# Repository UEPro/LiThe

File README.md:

# LiThe
Lichttheremin / Light-Theremin<br />

This PCB was designed for a Workshop in Germany, thus the documentation is in German. Contact me if you need a translation (Contact info in folder "Documentation", file "Anleitung_LiThe")

<b>AKF-WORKSHOP:</b></n>

Hallo ihr Lieben, ich hoffe ihr hattet alle ein tolles Festival und seid gut Heim gekommen. :)

Vielen Dank, dass ihr beim Workshop mitgemacht habt. Es hat mir riesigen Spaß gemacht, mit euch zu Arbeiten und ich hoffe auch ihr hattet Freude am basteln.

Solltet ihr irgendwelche Fragen oder Probleme haben, schreibt mir einfach über github oder schickt mir eine E-Mail (die Adresse steht in der Anleitung oben im Ordner "Documentation").

Ich werde außerdem eine Facebookseite einrichten, damit ihr mich einfacher kontaktieren könnt. Der Link dazu kommt dann hier her.

Schreibt mir gerne auch für weiteres Feedback und Vorschläge.

Nochmals Danke für die tolle Zeit mit euch und das nette Feedback :) Ich hoffe man sieht sich wieder.

Downloadanleitung:<br />
-Einzelne Datei: Rechtsklick auf die Datei → "Ziel speichern unter" anklicken<br />
-Ganzes Archiv: oben rechts den grünen Knopf "Clone or download" anklicken → "Download as ZIP" anklicken → ZIP Archiv entpacken

<br /><span xmlns:dct="http://purl.org/dc/terms/" property="dct:title">LiThe</span> by <a xmlns:cc="http://creativecommons.org/ns#" href="https://github.com/UEPro/" property="cc:attributionName" rel="cc:attributionURL">Useless Electronics Projects</a> is licensed under a <a rel="license" href="http://creativecommons.org/licenses/by-sa/4.0/">Creative Commons Attribution-ShareAlike 4.0 International License</a>.<br />

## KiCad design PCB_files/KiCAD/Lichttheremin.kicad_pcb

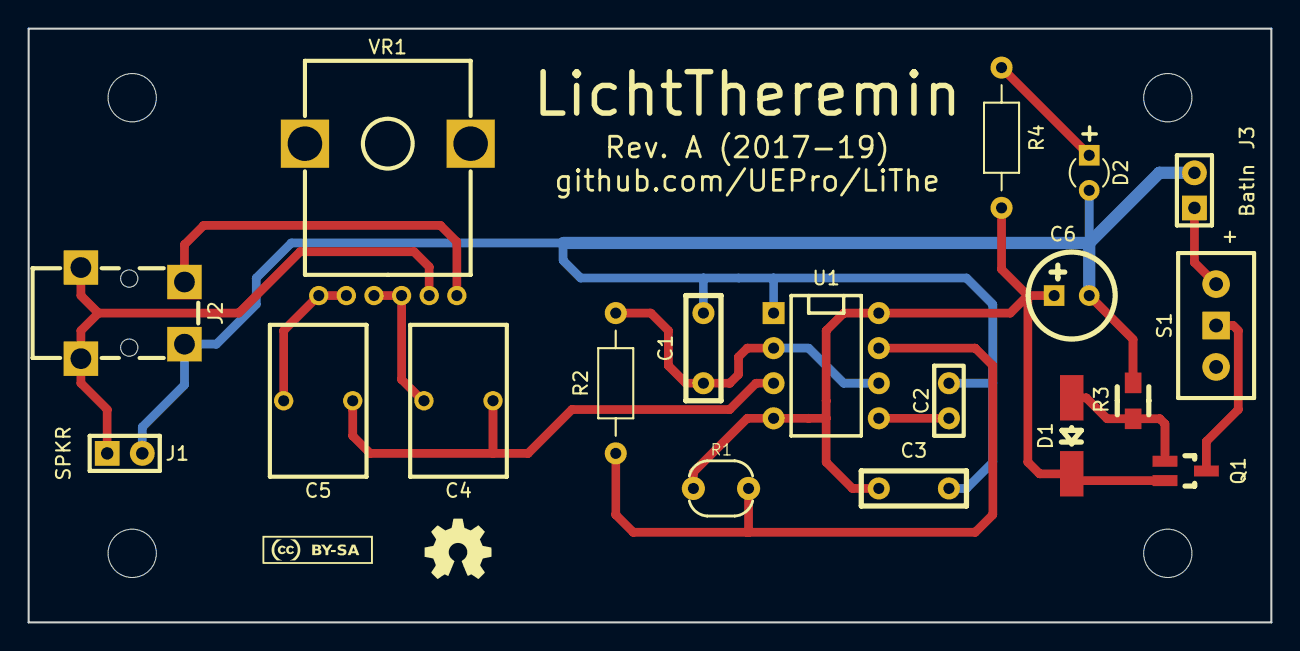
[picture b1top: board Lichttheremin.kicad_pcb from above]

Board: 2 copper layers, 90.0 x 43.0 mm, 25 parts (0 on the bottom side), 14 nets.

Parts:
C1, C3: 100n; C_rect-radial-bipolar-200mil-2,5x7mm
C2: 10n; C_rect-radial-bipolar-100mil-2x5mm
C4, C5: 2µ2; C-Rect_L7_W11_P5
C6: 220µ/16V; C_round-radial-polar-2,5mm-6,3mm
D1: 4V7; Diode_MiniMELF-Handsoldering
D2: 3mm/cyan; LED_2pin-3mm
Des*: Val*; MountingHole-3,5mm
Des*#2, Des*#3, Des*#4: Val*; MountingHole-3,5mm
J1: Speaker; PinArray-100mil-1x2
J2: Klinke-stereo; Lumberg-1503-07-Klinke-3,5mm
J3: BatIn; PinArray-100mil-1x2
Q1: FDN304; SOT23-Handsoldering
R1: LDR; SparkFun-PHOTOCELL
R2: 100; R_axial_400mil
R3: 10k; SMD0805-HandSoldering
R4: 10k; R_axial_400mil
S1: S_1P2T; S-Schiebeschalter_China_SPDT
U1: NE555; DIP-8_300
VAL: REF; oshw5mm
VAL#2: REF; CC-BY-SA_08mm_Fsi
VR1: 10k log; VR-Alps_R12L_vert

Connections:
+9V: C3.1, C6.1, D1.2, Q1.2, R1.1, R4.1, U1.4, U1.8
GND: C1.2, C2.2, C3.2, C6.2, D2.2, J1.2, J2.1, J3.2, R3.2, U1.1
unnamed: C1.1, R2.2, U1.2, U1.6
unnamed: C2.1, U1.5
unnamed: C4.1, C5.1, U1.3
unnamed: C4.2, VR1.1, VR1.2
unnamed: C5.2, VR1.4, VR1.5
unnamed: D1.1, Q1.1, R3.1
unnamed: D2.1, R4.2
unnamed: J1.1, J2.3, VR1.3
unnamed: J2.2, VR1.6
unnamed: J3.1, S1.3
unnamed: Q1.3, S1.2
unnamed: R1.2, R2.1, U1.7
